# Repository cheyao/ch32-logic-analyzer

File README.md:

# 200Msps 16ch logic analyzer + 20Msps oscilloscope

This is a cheap 200Msps logic analyzer with a 20Msps analog component. It uses USB 3.2 to send data to the computer, and can also act as a ch32h417 development board.

It is usable with pulseview delivering a beautiful interface and allowing you to view all kinds of diffrent protocols. And with voltage changing, it supports 1.2V, 3.3V and 5V opration modes.

The analog channels support 20Msps at 10bit accuracy, or 5MHz at 12bit accuracy. Input range is from 0V to 5V, and it supports external triggering too!

The bottom row of header breaks out GPIO pins of various protocols, allowing the board to also become a devboard that can be programed via USB.

---

The PCB is a 4-layered board in order to preserve signal intergity on the USB 3.2 data lines. With high-quality TI active components to preserve signal quality.

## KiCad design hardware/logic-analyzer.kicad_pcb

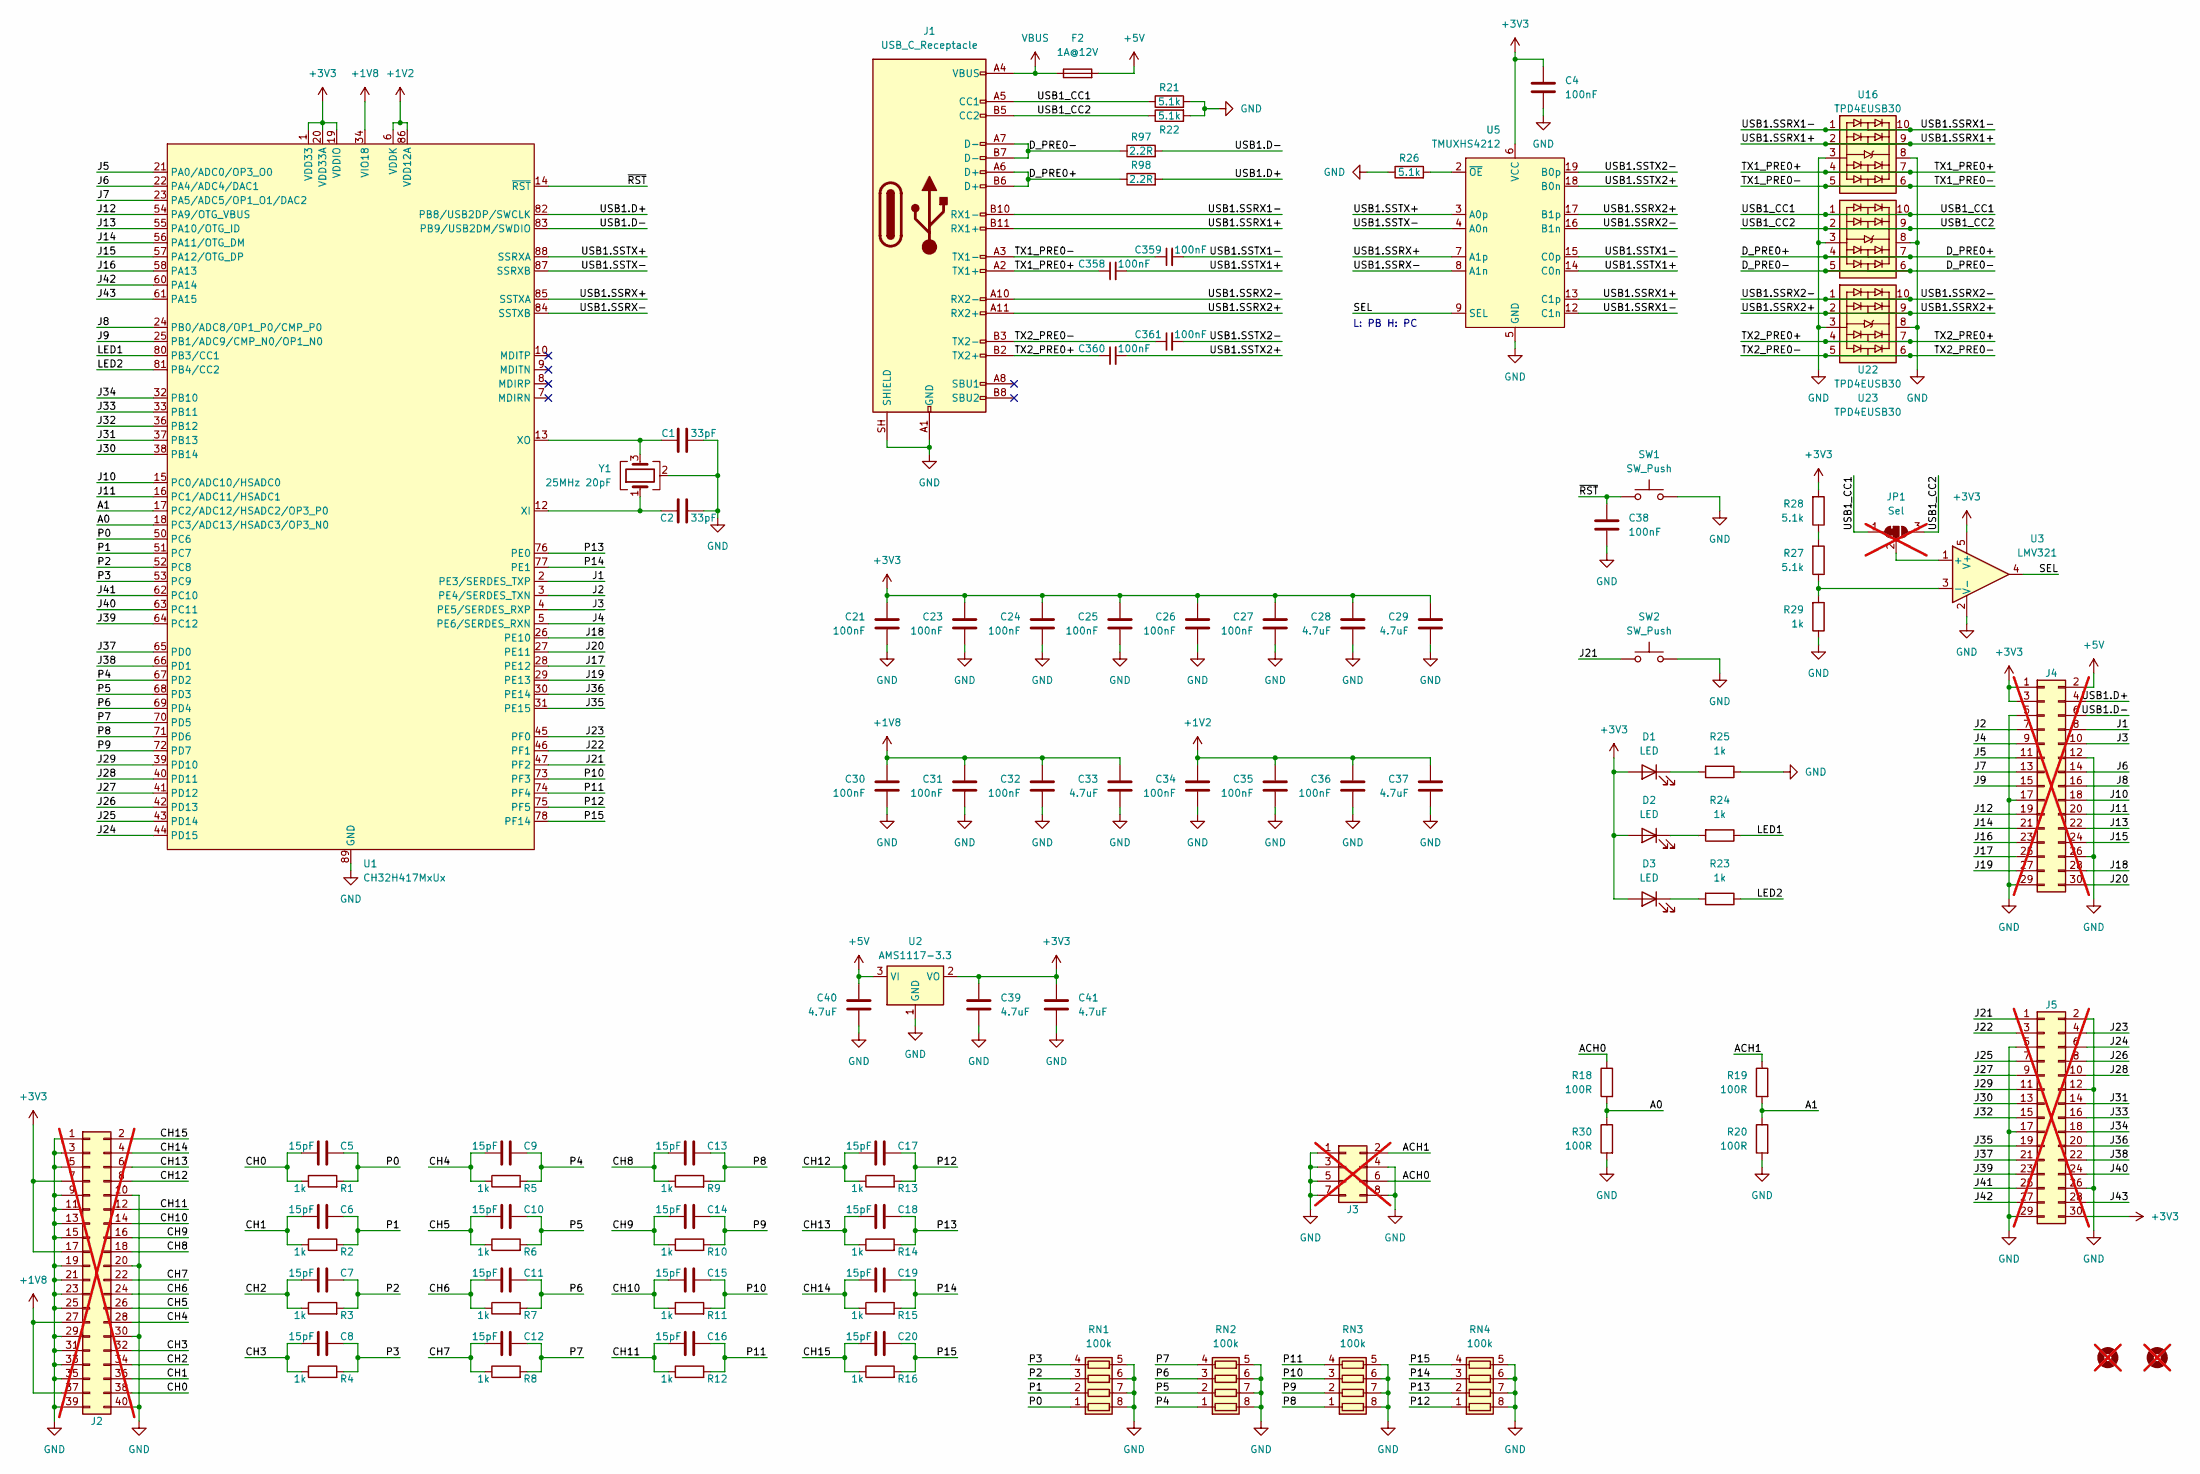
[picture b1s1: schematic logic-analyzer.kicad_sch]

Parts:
C1, C2: 33pF; C_0402_1005Metric; MPN GCM1555C1H330JA16J; LCSC Part # C5137486
C4, C21, C23, C24, C25, C26, C27, C30, C31, C32, C34, C35, C36, C38, C358, C359, C360, C361: 100nF; C_0402_1005Metric; MPN CC0402KRX7R7BB104; LCSC Part # C60474
C5, C6, C7, C8, C9, C10, C11, C12, C13, C14, C15, C16, C17, C18, C19, C20: 15pF; C_0402_1005Metric_Pad0.74x0.62mm_HandSolder; MPN VJ0402A150JXAAC; LCSC Part # C1548
C28, C29, C33, C37, C39, C40, C41: 4.7uF; C_0402_1005Metric; MPN GRM155R60G475ME87D; LCSC Part # C380302
D1, D2, D3: LED; LED_0402_1005Metric; LCSC Part # C51933306
F2: 1A@12V; Fuse_0805_2012Metric; LCSC Part # C46640991
H1, H2: MountingHole; Icy Electronics Logo; not fitted
J1: USB_C_Receptacle; USB_C_Receptacle_SHOU-HAN_24P-QT; LCSC Part # C2681555
J2: Conn_02x20; PinHeader_2x20_P1.27mm_Horizontal; LCSC Part # C2881906; not fitted
J3: Conn_02x04; PinHeader_2x04_P1.27mm_Horizontal; LCSC Part # C2881890; not fitted
J4, J5: Conn_02x15; PinHeader_2x15_P2.54mm_Vertical; LCSC Part # C56496; not fitted
JP1: Sel; SolderJumper-3_P1.3mm_Bridged12_RoundedPad1.0x1.5mm; not fitted
R1, R2, R3, R4, R5, R6, R7, R8, R9, R10, R11, R12, R13, R14, R15, R16: 1k; R_0402_1005Metric_Pad0.72x0.64mm_HandSolder; MPN RC0402FR-071KL; LCSC Part # C11702
R18, R19, R20, R30: 100R; R_0402_1005Metric; MPN MCS04020C1000FE000; LCSC Part # C705627
R21, R22, R26, R27, R28: 5.1k; R_0402_1005Metric; MPN AC0402FR-075K1L; LCSC Part # C852856
R23, R24, R25, R29: 1k; R_0402_1005Metric; MPN RC0402FR-071KL; LCSC Part # C852624
R97, R98: 2.2R; R_0402_1005Metric; MPN RC0402FR-072R2L; LCSC Part # C100632
RN1, RN2, RN3, RN4: 100k; R_Array_Convex_4x0603; MPN EXB-V8V104JV; LCSC Part # C110374
SW1, SW2: SW_Push; SW_Push_SPST_TSA016; LCSC Part # C2888428
U1: CH32H417MxUx; QFN-88-1EP_10x10mm_P0.4mm_EP5.7x5.7mm_ThermalVias; MPN CH32H417MEU6; LCSC Part # C54973456
U2: AMS1117-3.3; SOT-89-3; LCSC Part # C347256
U3: LMV321; SOT-353_SC-70-5; MPN LMV321IDCKT; LCSC Part # C3029047
U5: TMUXHS4212; DHVQFN-20-1EP_2.5x4.5mm_P0.5mm_EP1x3mm; MPN TMUXHS4212RKSR; LCSC Part # C2869871
U16, U22, U23: TPD4EUSB30; USON-10_2.5x1.0mm_P0.5mm; MPN TPD4EUSB30DQAR; LCSC Part # C558427
Y1: 25MHz 20pF; Crystal_SMD_2016-4Pin_2.0x1.6mm; MPN XT1220HJRGX25M00E; LCSC Part # C37635326

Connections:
+1V2: C34.1, C35.1, C36.1, C37.1, U1.6 (VDDK), U1.48 (VDDK), U1.86 (VDD12A)
+1V8: C30.1, C31.1, C32.1, C33.1, J2.27, J2.37, U1.34 (VIO18), U1.49 (VIO18), U1.79 (VIO18)
+3V3: C4.1, C21.1, C23.1, C24.1, C25.1, C26.1, C27.1, C28.1, C29.1, C39.1, C41.1, D1.2 (A), D2.2 (A), D3.2 (A), J2.7, J2.17, J4.1, J4.3, J5.30, R28.2, U1.1 (VDD33), U1.11 (VDD33), U1.19 (VDDIO), U1.20 (VDD33A), U1.35 (VDDIO), U1.59 (VDD33), U2.2 (VO), U3.5 (V+), U5.1 (RSVD1), U5.6 (VCC), U5.10 (RSVD2)
+5V: C40.1, F2.2, J4.2, U2.3 (VI)
/A0: R18.2, R30.1, U1.18 (PC3/ADC13/HSADC3/OP3_N0)
/A1: R19.2, R20.1, U1.17 (PC2/ADC12/HSADC2/OP3_P0)
/ACH0: J3.6, R18.1
/ACH1: J3.2, R19.1
/CH0: C5.1, J2.38, R1.1
/CH1: C6.1, J2.36, R2.1
/CH2: C7.1, J2.34, R3.1
/CH3: C8.1, J2.32, R4.1
/CH4: C9.1, J2.28, R5.1
/CH5: C10.1, J2.26, R6.1
/CH6: C11.1, J2.24, R7.1
/CH7: C12.1, J2.22, R8.1
/CH8: C13.1, J2.18, R9.1
/CH9: C14.1, J2.16, R10.1
/CH10: C15.1, J2.14, R11.1
/CH11: C16.1, J2.12, R12.1
/CH12: C17.1, J2.8, R13.1
/CH13: C18.1, J2.6, R14.1
/CH14: C19.1, J2.4, R15.1
/CH15: C20.1, J2.2, R16.1
/D_PRE0+: J1.A6 (D+), J1.B6 (D+), R98.1, U22.4, U22.7
/D_PRE0-: J1.A7 (D-), J1.B7 (D-), R97.1, U22.5, U22.6
/J1: J4.8, U1.2 (PE3/SERDES_TXP)
/J2: J4.7, U1.3 (PE4/SERDES_TXN)
/J3: J4.10, U1.4 (PE5/SERDES_RXP)
/J4: J4.9, U1.5 (PE6/SERDES_RXN)
/J5: J4.11, U1.21 (PA0/ADC0/OP3_O0)
/J6: J4.14, U1.22 (PA4/ADC4/DAC1)
/J7: J4.13, U1.23 (PA5/ADC5/OP1_O1/DAC2)
/J8: J4.16, U1.24 (PB0/ADC8/OP1_P0/CMP_P0)
/J9: J4.15, U1.25 (PB1/ADC9/CMP_N0/OP1_N0)
/J10: J4.18, U1.15 (PC0/ADC10/HSADC0)
/J11: J4.20, U1.16 (PC1/ADC11/HSADC1)
/J12: J4.19, U1.54 (PA9/OTG_VBUS)
/J13: J4.22, U1.55 (PA10/OTG_ID)
/J14: J4.21, U1.56 (PA11/OTG_DM)
/J15: J4.24, U1.57 (PA12/OTG_DP)
/J16: J4.23, U1.58 (PA13)
/J17: J4.25, U1.28 (PE12)
/J18: J4.28, U1.26 (PE10)
/J19: J4.27, U1.29 (PE13)
/J20: J4.30, U1.27 (PE11)
/J21: J5.1, SW2.2, U1.47 (PF2)
/J22: J5.3, U1.46 (PF1)
/J23: J5.4, U1.45 (PF0)
/J24: J5.6, U1.44 (PD15)
/J25: J5.7, U1.43 (PD14)
/J26: J5.8, U1.42 (PD13)
/J27: J5.9, U1.41 (PD12)
/J28: J5.10, U1.40 (PD11)
/J29: J5.11, U1.39 (PD10)
/J30: J5.13, U1.38 (PB14)
/J31: J5.14, U1.37 (PB13)
/J32: J5.15, U1.36 (PB12)
/J33: J5.16, U1.33 (PB11)
/J34: J5.18, U1.32 (PB10)
/J35: J5.19, U1.31 (PE15)
/J36: J5.20, U1.30 (PE14)
/J37: J5.21, U1.65 (PD0)
/J38: J5.22, U1.66 (PD1)
/J39: J5.23, U1.64 (PC12)
/J40: J5.24, U1.63 (PC11)
/J41: J5.25, U1.62 (PC10)
/J42: J5.27, U1.60 (PA14)
/J43: J5.28, U1.61 (PA15)
/LED1: R24.1, U1.80 (PB3/CC1)
/LED2: R23.1, U1.81 (PB4/CC2)
/P0: C5.2, R1.2, RN1.1 (R1.1), U1.50 (PC6)
/P1: C6.2, R2.2, RN1.2 (R2.1), U1.51 (PC7)
/P2: C7.2, R3.2, RN1.3 (R3.1), U1.52 (PC8)
/P3: C8.2, R4.2, RN1.4 (R4.1), U1.53 (PC9)
/P4: C9.2, R5.2, RN2.1 (R1.1), U1.67 (PD2)
/P5: C10.2, R6.2, RN2.2 (R2.1), U1.68 (PD3)
/P6: C11.2, R7.2, RN2.3 (R3.1), U1.69 (PD4)
/P7: C12.2, R8.2, RN2.4 (R4.1), U1.70 (PD5)
/P8: C13.2, R9.2, RN3.1 (R1.1), U1.71 (PD6)
/P9: C14.2, R10.2, RN3.2 (R2.1), U1.72 (PD7)
/P10: C15.2, R11.2, RN3.3 (R3.1), U1.73 (PF3)
/P11: C16.2, R12.2, RN3.4 (R4.1), U1.74 (PF4)
/P12: C17.2, R13.2, RN4.1 (R1.1), U1.75 (PF5)
/P13: C18.2, R14.2, RN4.2 (R2.1), U1.76 (PE0)
/P14: C19.2, R15.2, RN4.3 (R3.1), U1.77 (PE1)
/P15: C20.2, R16.2, RN4.4 (R4.1), U1.78 (PF14)
/SEL: U3.4, U5.9 (SEL)
/TX1_PRE0+: C358.1, J1.A2 (TX1+), U16.4, U16.7
/TX1_PRE0-: C359.1, J1.A3 (TX1-), U16.5, U16.6
/TX2_PRE0+: C360.1, J1.B2 (TX2+), U23.4, U23.7
/TX2_PRE0-: C361.1, J1.B3 (TX2-), U23.5, U23.6
/USB1.D+: J4.4, R98.2, U1.82 (PB8/USB2DP/SWCLK)
/USB1.D-: J4.6, R97.2, U1.83 (PB9/USB2DM/SWDIO)
/USB1.SSRX1+: J1.B11 (RX1+), U5.13 (C1p), U16.2, U16.9
/USB1.SSRX1-: J1.B10 (RX1-), U5.12 (C1n), U16.1, U16.10
/USB1.SSRX2+: J1.A11 (RX2+), U5.17 (B1p), U23.2, U23.9
/USB1.SSRX2-: J1.A10 (RX2-), U5.16 (B1n), U23.1, U23.10
/USB1.SSRX+: U1.85 (SSTXA), U5.7 (A1p)
/USB1.SSRX-: U1.84 (SSTXB), U5.8 (A1n)
/USB1.SSTX1+: C358.2, U5.14 (C0n)
/USB1.SSTX1-: C359.2, U5.15 (C0p)
/USB1.SSTX2+: C360.2, U5.18 (B0n)
/USB1.SSTX2-: C361.2, U5.19 (B0p)
/USB1.SSTX+: U1.88 (SSRXA), U5.3 (A0p)
/USB1.SSTX-: U1.87 (SSRXB), U5.4 (A0n)
/USB1_CC1: J1.A5 (CC1), JP1.1 (A), R21.1, U22.1, U22.10
/USB1_CC2: J1.B5 (CC2), JP1.3 (B), R22.1, U22.2, U22.9
/~RST: C38.1, SW1.2, U1.14 (~RST)
GND: C1.1, C2.1, C4.2, C21.2, C23.2, C24.2, C25.2, C26.2, C27.2, C28.2, C29.2, C30.2, C31.2, C32.2, C33.2, C34.2, C35.2, C36.2, C37.2, C38.2, C39.2, C40.2, C41.2, J1.A1 (GND), J1.A12 (GND), J1.B1 (GND), J1.B12 (GND), J1.SH (SHIELD), J2.1, J2.3, J2.5, J2.9, J2.10, J2.11, J2.13, J2.15, J2.19, J2.20, J2.21, J2.23, J2.25, J2.29, J2.30, J2.31, J2.33, J2.35, J2.39, J2.40, J3.1, J3.3, J3.4, J3.5, J3.7, J3.8, J4.5, J4.12, J4.17, J4.26, J4.29, J5.2, J5.5, J5.12, J5.17, J5.26, J5.29, R20.2, R21.2, R22.2, R25.1, R26.1, R29.1, R30.2, RN1.5 (R4.2), RN1.6 (R3.2), RN1.7 (R2.2), RN1.8 (R1.2), RN2.5 (R4.2), RN2.6 (R3.2), RN2.7 (R2.2), RN2.8 (R1.2), RN3.5 (R4.2), RN3.6 (R3.2), RN3.7 (R2.2), RN3.8 (R1.2), RN4.5 (R4.2), RN4.6 (R3.2), RN4.7 (R2.2), RN4.8 (R1.2), SW1.1, SW2.1, U1.89 (GND), U2.1 (GND), U3.2 (V-), U5.5 (GND), U5.11 (GND), U5.20 (GND), U5.21 (GND), U16.3, U16.8, U22.3, U22.8, U23.3, U23.8, Y1.2 (G), Y1.4 (G)
unnamed: D1.1 (K), R25.2
unnamed: D2.1 (K), R24.2
unnamed: D3.1 (K), R23.2
unnamed: JP1.2 (C), U3.1 (+)
unnamed: R27.2, R28.1
unnamed: C2.2, U1.12 (XI), Y1.1
unnamed: C1.2, U1.13 (XO), Y1.3
unnamed: R27.1, R29.2, U3.3 (-)
unnamed: R26.2, U5.2 (~OE)
VBUS: F2.1, J1.A4 (VBUS), J1.A9 (VBUS), J1.B4 (VBUS), J1.B9 (VBUS)

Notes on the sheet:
L: PB H: PC

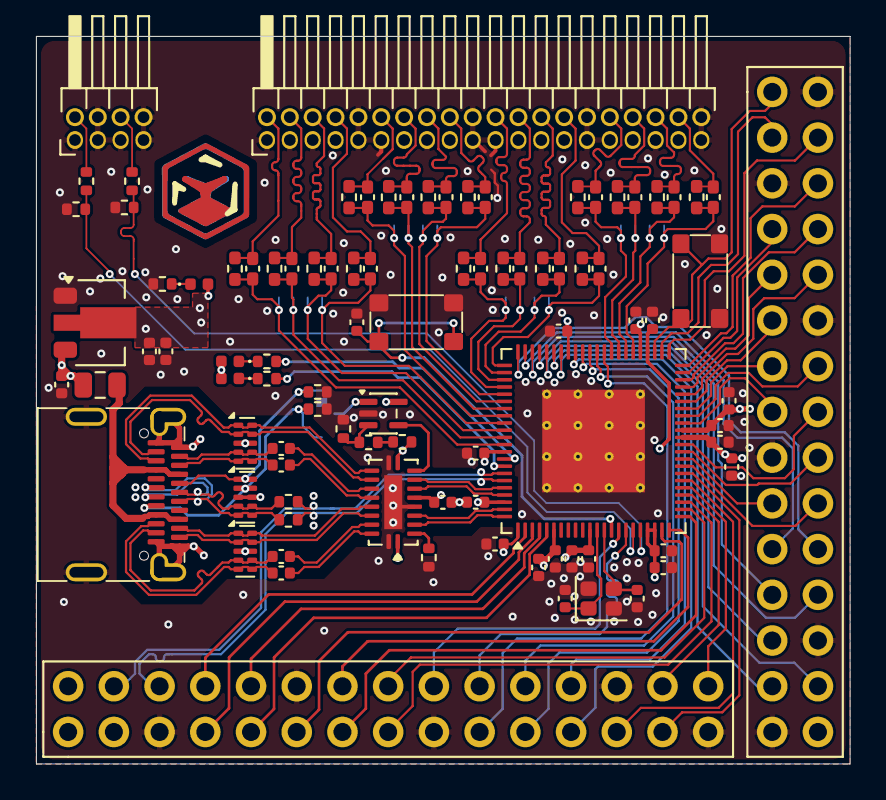
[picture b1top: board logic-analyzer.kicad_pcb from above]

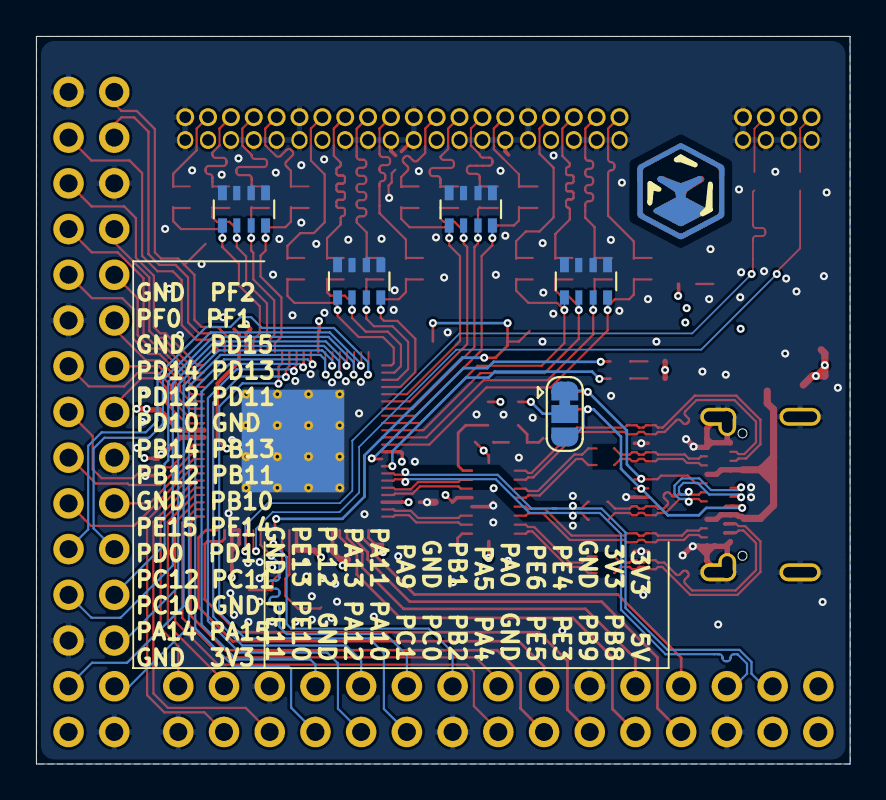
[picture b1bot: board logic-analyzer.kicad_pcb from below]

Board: 4 copper layers, 45.2 x 40.4 mm, 100 parts (6 on the bottom side), 120 nets.

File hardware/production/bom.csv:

Designator,Footprint,Quantity,Value,LCSC Part #
"C1, C2",0402,2,33pF,C5137486
"C10, C11, C12, C13, C14, C15, C16, C17, C18, C19, C20, C5, C6, C7, C8, C9",0402,16,15pF,C1548
"C21, C23, C24, C25, C26, C27, C30, C31, C32, C34, C35, C358, C359, C36, C360, C361, C38, C4",0402,18,100nF,C60474
"C28, C29, C33, C37, C39, C40, C41",0402,7,4.7uF,C380302
"D1, D2, D3",0402,3,LED,C51933306
F2,0805,1,1A@12V,C46640991
J1,USB_C_Receptacle_SHOU-HAN_24P-QT,1,USB_C_Receptacle,C2681555
J2,PinHeader_2x20_P1.27mm_Horizontal,1,Conn_02x20,C2881906
J3,PinHeader_2x04_P1.27mm_Horizontal,1,Conn_02x04,C2881890
"J4, J5",PinHeader_2x15_P2.54mm_Vertical,2,Conn_02x15,C56496
"R1, R10, R11, R12, R13, R14, R15, R16, R2, R23, R24, R25, R29, R3, R4, R5, R6, R7, R8, R9",0402,20,1k,C106235
"R18, R19, R20, R30",0402,4,100R,C106232
"R21, R22, R26, R27, R28",0402,5,5.1k,C105872
"R97, R98",0402,2,2.2R,C54920775
"RN1, RN2, RN3, RN4",R_Array_Convex_4x0603,4,100k,C110374
"SW1, SW2",SW_Push_SPST_TSA016,2,SW_Push,C2888427
U1,QFN-88-1EP_10x10mm_P0.4mm_EP5.7x5.7mm_ThermalVias,1,CH32H417MxUx,C54973456
"U16, U22, U23",USON-10_2.5x1.0mm_P0.5mm,3,TPD4EUSB30,C558427
U2,SOT-89-3,1,AMS1117-3.3,C347256
U3,SOT-353_SC-70-5,1,LMV321,C3029047
U5,DHVQFN-20-1EP_2.5x4.5mm_P0.5mm_EP1x3mm,1,TMUXHS4212,C2869871
Y1,Crystal_SMD_2016-4Pin_2.0x1.6mm,1,25MHz 20pF,C37635326

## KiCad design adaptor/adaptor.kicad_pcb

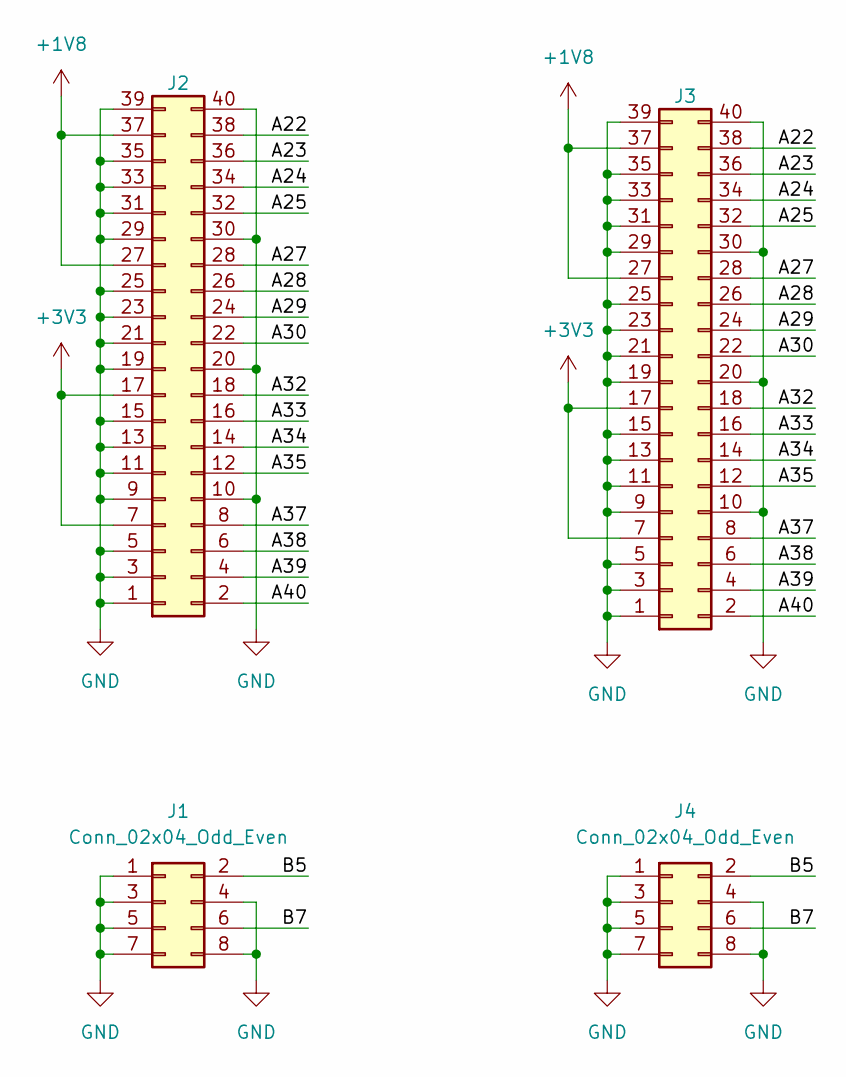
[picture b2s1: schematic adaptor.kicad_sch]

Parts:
J1: Conn_02x04_Odd_Even; Edge_1.27mm_02x04
J2: Conn_02x20; Edge_1.27mm_02x20; LCSC Part # C2881906
J3: Conn_02x20; Edge_2.54mm_02x20; LCSC Part # C2881906
J4: Conn_02x04_Odd_Even; Edge_2.54mm_02x04

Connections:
+1V8: J2.27, J2.37, J3.27, J3.37
+3V3: J2.7, J2.17, J3.7, J3.17
/A22: J2.38, J3.38
/A23: J2.36, J3.36
/A24: J2.34, J3.34
/A25: J2.32, J3.32
/A27: J2.28, J3.28
/A28: J2.26, J3.26
/A29: J2.24, J3.24
/A30: J2.22, J3.22
/A32: J2.18, J3.18
/A33: J2.16, J3.16
/A34: J2.14, J3.14
/A35: J2.12, J3.12
/A37: J2.8, J3.8
/A38: J2.6, J3.6
/A39: J2.4, J3.4
/A40: J2.2, J3.2
/B5: J1.2, J4.2
/B7: J1.6, J4.6
GND: J1.1, J1.3, J1.4, J1.5, J1.7, J1.8, J2.1, J2.3, J2.5, J2.9, J2.10, J2.11, J2.13, J2.15, J2.19, J2.20, J2.21, J2.23, J2.25, J2.29, J2.30, J2.31, J2.33, J2.35, J2.39, J2.40, J3.1, J3.3, J3.5, J3.9, J3.10, J3.11, J3.13, J3.15, J3.19, J3.20, J3.21, J3.23, J3.25, J3.29, J3.30, J3.31, J3.33, J3.35, J3.39, J3.40, J4.1, J4.3, J4.4, J4.5, J4.7, J4.8

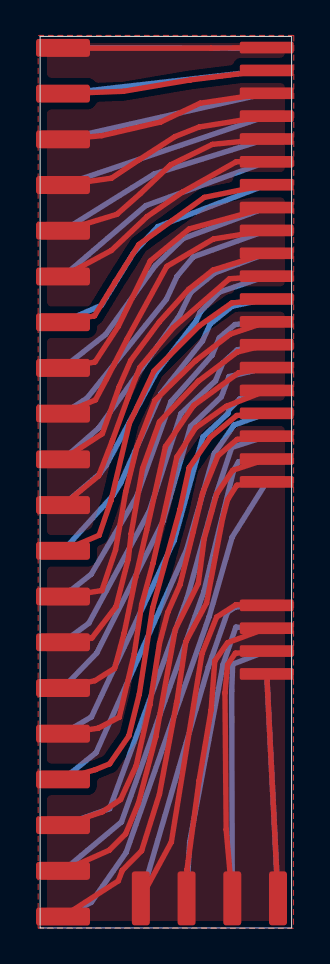
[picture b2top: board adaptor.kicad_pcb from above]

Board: 2 copper layers, 14.0 x 49.5 mm, 4 parts (0 on the bottom side), 21 nets.

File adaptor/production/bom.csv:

Designator,Footprint,Quantity,Value,LCSC Part #
J1,Edge_1.27mm_02x04,1,Conn_02x04_Odd_Even,
J2,Edge_1.27mm_02x20,1,Conn_02x20,C2881906
J3,Edge_2.54mm_02x20,1,Conn_02x20,C2881906
J4,Edge_2.54mm_02x04,1,Conn_02x04_Odd_Even,

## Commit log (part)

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2026-05-30 CH9441P variant
2026-05-30 Change CH9441P into something available
2026-06-02 Readme
2026-06-05 Stencil
2026-06-13 General improvements
